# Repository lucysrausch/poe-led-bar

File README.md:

# poe-led-bar

Important! I did not have a chance to write docs for this project yet, so:
The hardware is proven at this point and people have successfully ordered and used PCBs based off this repo, with one exception.

The PCB design has a minor bug with the polarity of one of the LEDs inside the ethernet jack.
In rev1.0 of the PCB design, this is not only causing the LED to not work but also the entire ethernet link, because the LEDs are also used as strapping pins to configure the PHY.

The workaround I used is to use this RJ45 jack, which has a bicolor LED so polarity doesn't matter:
https://www.digikey.com/en/products/detail/adam-tech/MTJ-88TX1-FSD-LV/9832786
You could use https://www.digikey.com/en/products/detail/adam-tech/MTJ-88TX1-LV/9832558 which is in stock.

If you dont particularly care about the LEDs in the jack, you can also just get a passive jack without LEDs and solder a 1k SMD resistor across the pads for the LEDs. That should also work fine to configure the PHY.

I will fix this in a future release so more common jacks like the ones stocked at JLC and LCSC can be used.

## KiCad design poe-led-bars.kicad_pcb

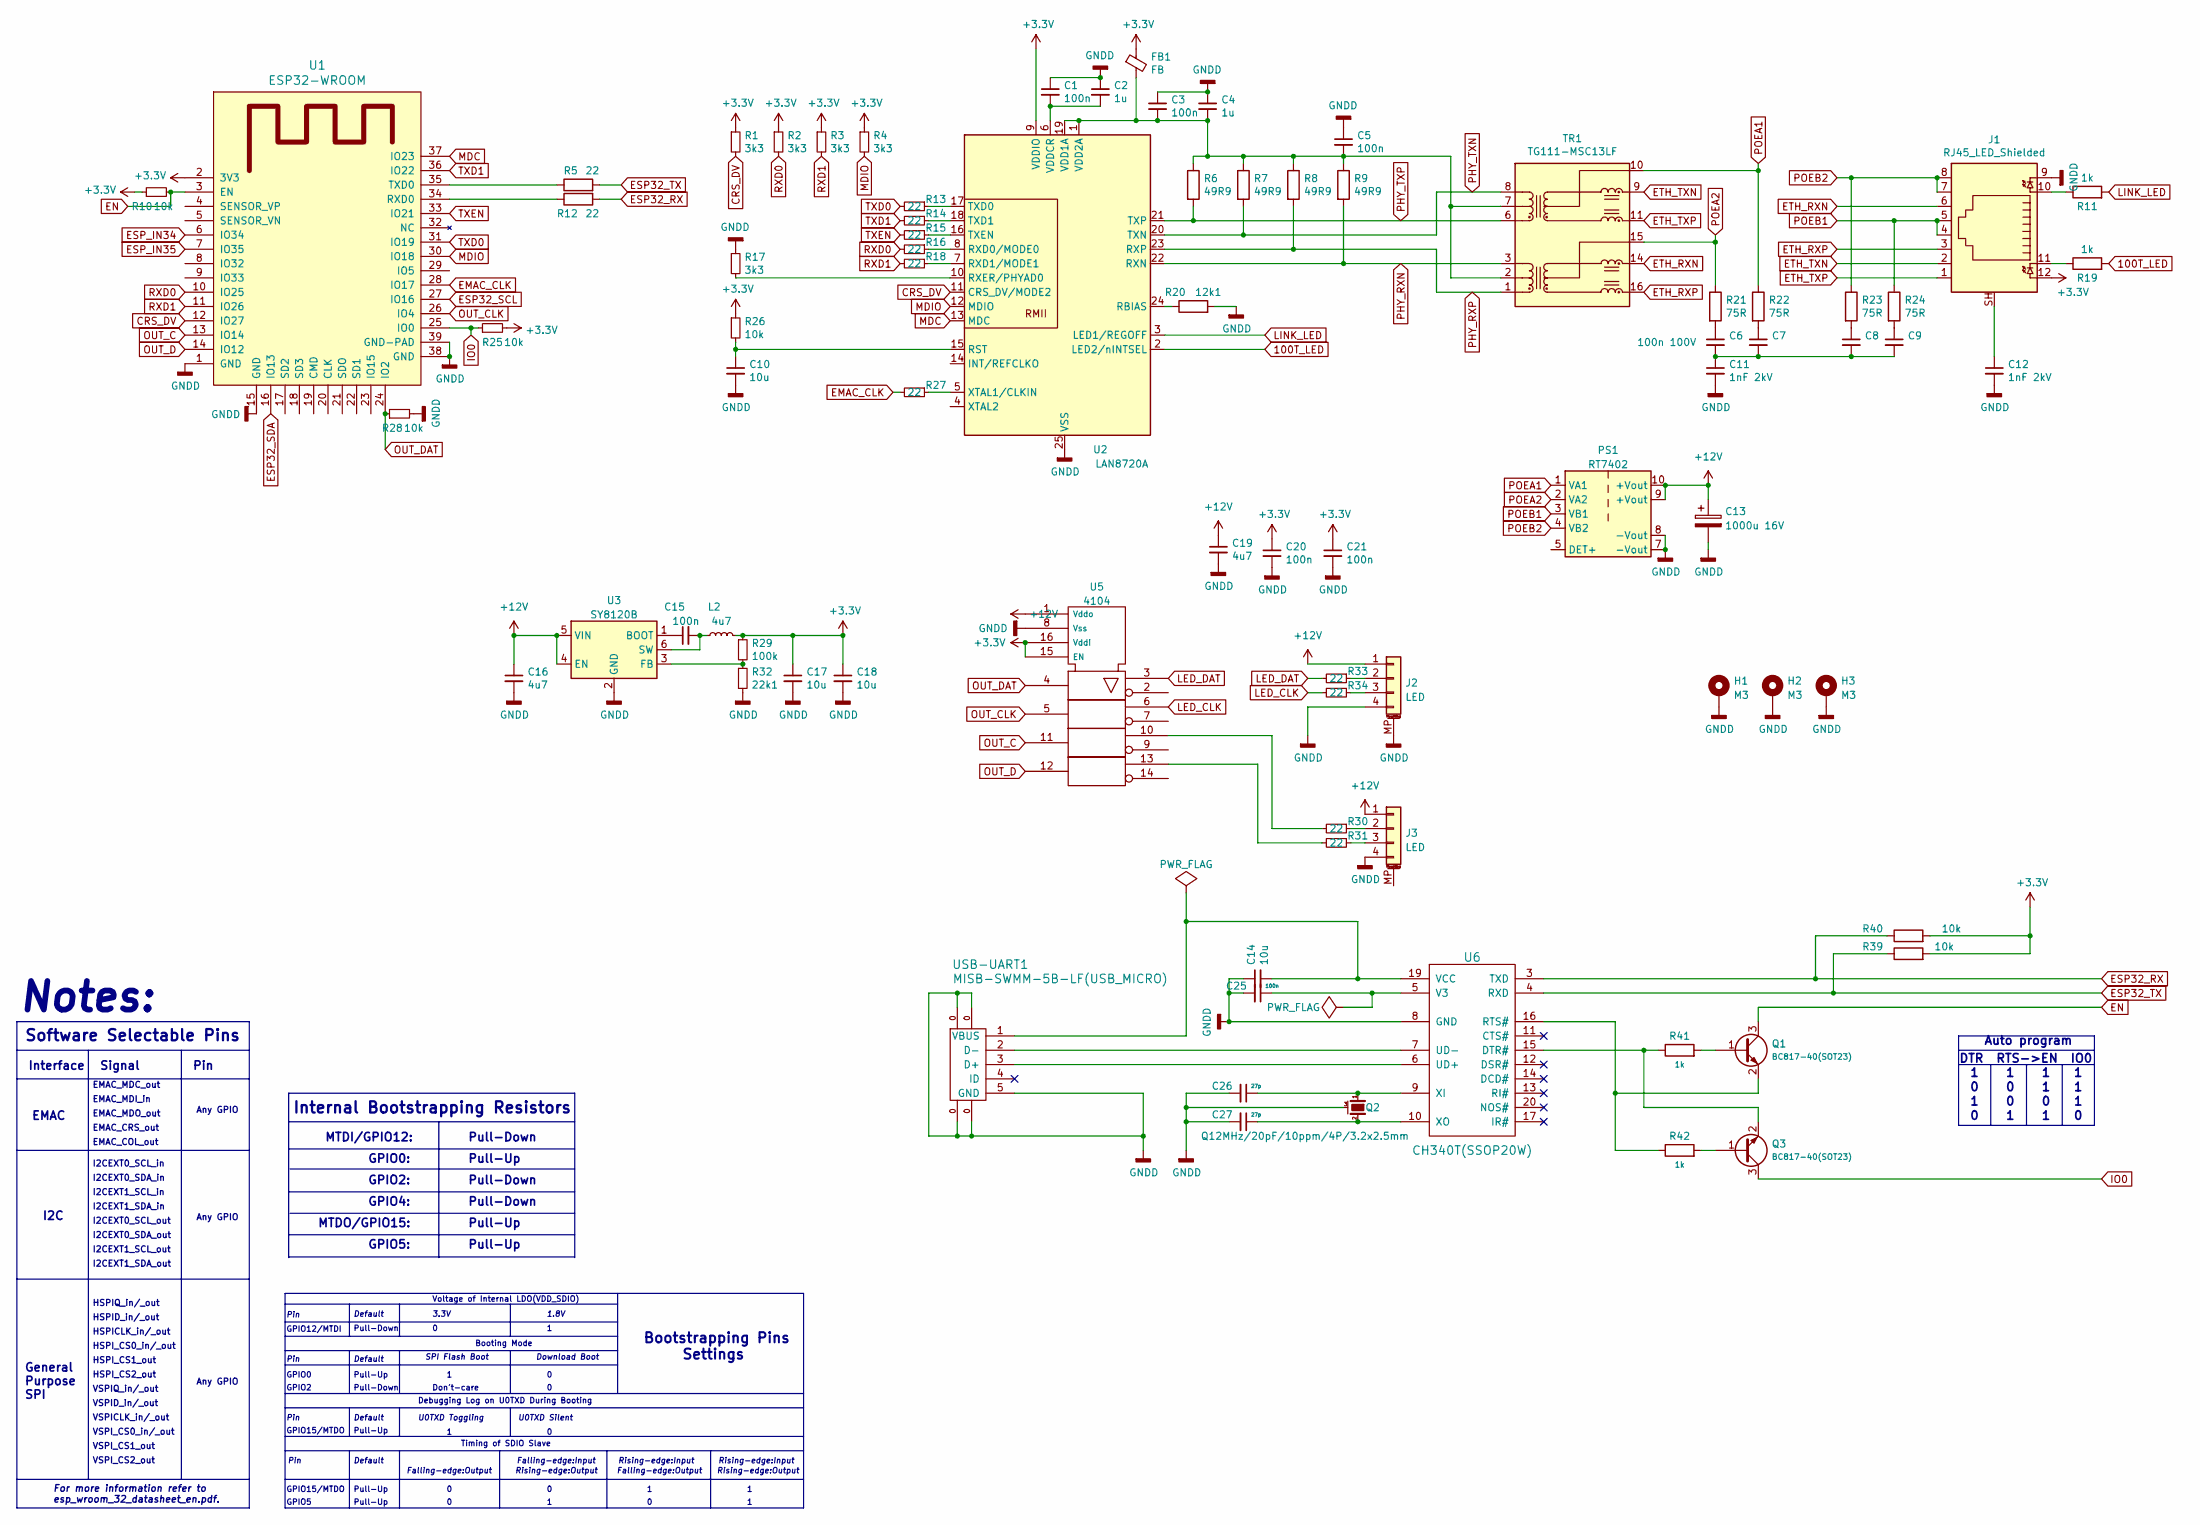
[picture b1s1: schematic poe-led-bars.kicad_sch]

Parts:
C1, C3, C5, C15, C20, C21, C25: 100n; C_0402
C2, C4: 1u; C_0402
C6, C7, C8, C9: 100n 100V; C_0603
C10, C14, C17, C18: 10u; C_0603
C11, C12: 1nF 2kV; C_1206_3216Metric
C13: 1000u 16V
C16, C19: 4u7; C_0603
C26, C27: 27p; C_0402
FB1: FB; L_0402
H1, H2, H3: M3
J1: RJ45_LED_Shielded; RJ45_Cetus_J1B1211CCD_Horizontal
J2, J3: LED
L2: 4u7
PS1: RT7402; Converter_DCDC_XP_POWER-IAxxxxD_THT
Q1, Q3: BC817-40(SOT23); SOT-23
Q2: Q12MHz/20pF/10ppm/4P/3.2x2.5mm; TSX-3.2x2.5mm_GND(3)
R1, R2, R3, R4, R17: 3k3; R_0402
R5, R12, R13, R14, R15, R16, R18, R27, R30, R31, R33, R34: 22; R_0402
R6, R7, R8, R9: 49R9; R_0402
R10, R25, R26, R28, R39, R40: 10k; R_0402
R11, R19, R41, R42: 1k; R_0402
R20: 12k1; R_0402
R21, R22, R23, R24: 75R; R_0402
R29: 100k; R_0402
R32: 22k1; R_0402
TR1: TG111-MSC13LF; XFMR_H1102NLT
U1: ESP32-WROOM; ESP32-WROOM-32U
U2: LAN8720A; QFN-24-1EP_4x4mm_P0.5mm_EP2.6x2.6mm
U3: SY8120B; SOT-23-6
U5: 4104; SO-16_3.9x9.9mm_P1.27mm
U6: CH340T(SSOP20W); SSOP-20W
USB-UART1: MISB-SWMM-5B-LF(USB_MICRO); USB-MICRO_MISB-SWMM-5B_LF

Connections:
100T_LED: R19.2, U2.2 (LED2/nINTSEL)
+3V3: C17.1, C18.1, C20.1, C21.1, FB1.1, J1.12, L2.2, R1.1, R2.1, R3.1, R4.1, R10.1, R25.2, R26.1, R29.1, R39.2, R40.2, U1.2 (3V3), U2.9 (VDDIO), U5.15 (EN), U5.16 (Vddi)
+12V: C13.1, C16.1, C19.1, J2.1, J3.1, PS1.9 (+Vout), PS1.10 (+Vout), U3.4 (EN), U3.5 (VIN), U5.1 (Vddo)
CRS_DV: R1.2, U1.12 (IO27), U2.11 (CRS_DV/MODE2)
EMAC_CLK: R27.2, U1.28 (IO17)
EN: Q1.3 (C), R10.2, U1.3 (EN)
ESP32_RX: R12.2, R40.1, U6.3 (TXD)
ESP32_SCL: U1.27 (IO16)
ESP32_SDA: U1.16 (IO13)
ESP32_TX: R5.2, R39.1, U6.4 (RXD)
ESP_IN34: U1.6 (IO34)
ESP_IN35: U1.7 (IO35)
ETH_RXN: J1.6, TR1.14 (MTX2-)
ETH_RXP: J1.3, TR1.16 (MTX2+)
ETH_TXN: J1.2, TR1.9 (MTX2-)
ETH_TXP: J1.1, TR1.11 (MTX2+)
GNDD: C1.1, C2.1, C3.1, C4.1, C5.1, C10.2, C11.2, C12.2, C13.2, C14.1, C16.2, C17.2, C18.2, C19.2, C20.2, C21.2, C25.2, C26.2, C27.2, H1.1, H2.1, H3.1, J1.9, J2.4, J2.MP (MountPin), J3.4, PS1.7 (-Vout), PS1.8 (-Vout), Q2.3 (case), R17.1, R20.2, R28.2, R32.2, U1.1 (GND), U1.15 (GND), U1.38 (GND), U1.39 (GND-PAD), U2.25 (VSS), U3.2 (GND), U5.8 (Vss), U6.8 (GND), USB-UART1.0, USB-UART1.5 (GND)
IO0: Q3.3 (C), R25.1, U1.25 (IO0)
LED_CLK: R34.2, U5.6
LED_DAT: R33.2, U5.3
LINK_LED: R11.2, U2.3 (LED1/REGOFF)
MDC: U1.37 (IO23), U2.13 (MDC)
MDIO: R4.2, U1.30 (IO18), U2.12 (MDIO)
unnamed: C1.2, C2.2, U2.6 (VDDCR)
unnamed: C3.2, C4.2, C5.2, FB1.2, R6.1, R7.1, R8.1, R9.1, TR1.2 (TCT2), TR1.7 (TCT2), U2.1 (VDD2A), U2.19 (VDD1A)
unnamed: C6.1, R21.2
unnamed: C7.1, R22.2
unnamed: C8.1, R23.2
unnamed: C9.1, R24.2
unnamed: C10.1, R26.2, U2.15 (RST)
unnamed: C6.2, C7.2, C8.2, C9.2, C11.1
unnamed: C12.1, J1.SH
unnamed: C14.2, U6.19 (VCC), USB-UART1.1 (VBUS)
unnamed: C15.1, U3.1 (BOOT)
unnamed: C15.2, L2.1, U3.6 (SW)
unnamed: C25.1, U6.5 (V3)
unnamed: C26.1, Q2.1, U6.9 (XI)
unnamed: C27.1, Q2.2, U6.10 (XO)
unnamed: J1.10, R11.1
unnamed: J1.11, R19.1
unnamed: J2.2, R33.1
unnamed: J2.3, R34.1
unnamed: J3.2, R30.1
unnamed: J3.3, R31.1
unnamed: Q1.1 (B), R41.2
unnamed: Q1.2 (E), R42.1, U6.16 (RTS#)
unnamed: Q3.1 (B), R42.2
unnamed: Q3.2 (E), R41.1, U6.15 (DTR#)
unnamed: R5.1, U1.35 (TXD0)
unnamed: R12.1, U1.34 (RXD0)
unnamed: R13.1, U2.17 (TXD0)
unnamed: R14.1, U2.18 (TXD1)
unnamed: R15.1, U2.16 (TXEN)
unnamed: R16.1, U2.8 (RXD0/MODE0)
unnamed: R17.2, U2.10 (RXER/PHYAD0)
unnamed: R18.1, U2.7 (RXD1/MODE1)
unnamed: R20.1, U2.24 (RBIAS)
unnamed: R27.1, U2.5 (XTAL1/CLKIN)
unnamed: R29.2, R32.1, U3.3 (FB)
unnamed: R30.2, U5.10
unnamed: R31.2, U5.13
unnamed: U6.6 (UD+), USB-UART1.3 (D+)
unnamed: U6.7 (UD-), USB-UART1.2 (D-)
OUT_C: U1.13 (IO14), U5.11
OUT_CLK: U1.26 (IO4), U5.5
OUT_D: U1.14 (IO12), U5.12
OUT_DAT: R28.1, U1.24 (IO2), U5.4
PHY_RXN: R9.2, TR1.3 (TD2-), U2.22 (RXN)
PHY_RXP: R8.2, TR1.1 (TD2+), U2.23 (RXP)
PHY_TXN: R7.2, TR1.8 (TD2-), U2.20 (TXN)
PHY_TXP: R6.2, TR1.6 (TD2+), U2.21 (TXP)
POEA1: PS1.1 (VA1), R22.1, TR1.10 (MCT2)
POEA2: PS1.2 (VA2), R21.1, TR1.15 (MCT2)
POEB1: J1.4, J1.5, PS1.3 (VB1), R24.1
POEB2: J1.7, J1.8, PS1.4 (VB2), R23.1
RXD0: R2.2, R16.2, U1.10 (IO25)
RXD1: R3.2, R18.2, U1.11 (IO26)
TXD0: R13.2, U1.31 (IO19)
TXD1: R14.2, U1.36 (IO22)
TXEN: R15.2, U1.33 (IO21)

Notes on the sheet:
Internal Bootstrapping Resistors
Pull-Up
I2CEXT0_SDA_out
Signal
Booting Mode
Rising-edge:Output
Download Boot
Any GPIO
1.8V
HSPI_CS1_out
Default
GPIO5:
Auto program
Pin
3.3V
GPIO5
Don't-care
GPIO15/MTDO
VSPIQ_in/_out
EMAC_CRS_out
HSPI_CS0_in/_out
GPIO0:
Debugging Log on U0TXD During Booting
I2CEXT0_SDA_in
I2CEXT0_SCL_out
I2C
General Purpose SPI
HSPI_CS2_out
Pull-Down
Software Selectable Pins
I2CEXT0_SCL_in
VSPI_CS0_in/_out
Falling-edge:Input
Voltage of Internal LDO(VDD_SDIO)
Notes:
GPIO2
Rising-edge:Input
VSPI_CS1_out
MTDO/GPIO15:
EMAC_MDI_in

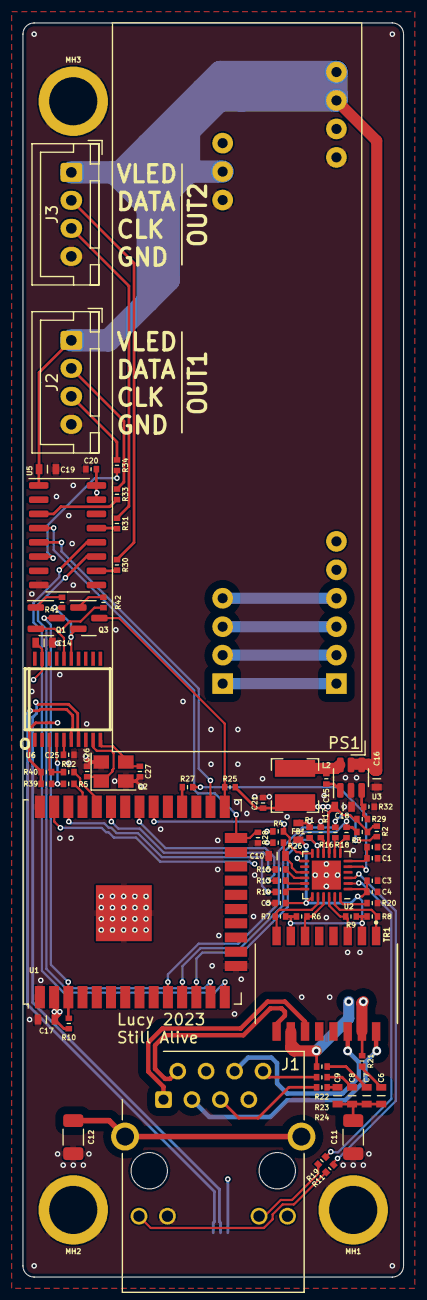
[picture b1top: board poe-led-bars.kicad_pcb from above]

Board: 4 copper layers, 34.0 x 112.0 mm, 80 parts (1 on the bottom side), 76 nets.

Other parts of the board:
MH1, MH2, MH3: Fiducial_0.5mm_Mask1.5mm

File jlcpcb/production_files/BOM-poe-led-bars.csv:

Comment,Designator,Footprint,LCSC
FB,FB1,C_0603,C1002
1k,"R11,R19,R41,R42",R_0402,C11702
100n,"C1,C15,C20,C21,C25,C3,C5",C_0402,C1525
27p,"C26,C27",C_0402,C1557
100n 100V,"C6,C7,C8,C9",C_0603,C15725
4u7,L2,L_Bourns-SRN4018,C167828
22k1,R32,R_0402,C170263
4u7,"C16,C19",C_0603,C19666
22,"R12,R13,R14,R15,R16,R18,R27,R30,R31,R33,R34,R5",R_0402,C25092
49R9,"R6,R7,R8,R9",R_0402,C25120
75R,"R21,R22,R23,R24",R_0402,C25133
100k,R29,R_0402,C25741
10k,"R10,R25,R26,R28,R39,R40",R_0402,C25744
12k1,R20,R_0402,C25852
3k3,"R1,R17,R2,R3,R4",R_0402,C25890
Fiducial_0.5mm_Mask1.5mm,"MH1,MH2,MH3",Fiducial_0.5mm_Mask1.5mm,C2915633
RJ45_LED_Shielded,J1,RJ45_Cetus_J1B1211CCD_Horizontal,C363238
BC817-40(SOT23),"Q1,Q3",SOT-23,C380921
LAN8720A,U2,QFN-24-1EP_4x4mm_P0.5mm_EP2.6x2.6mm,C45223
TG111-MSC13LF,TR1,XFMR_H1102NLT,C510548
1u,"C2,C4",C_0402,C52923
ESP32-WROOM,U1,ESP32-WROOM-32U,C701345
4104,U5,SO-16_3.9x9.9mm_P1.27mm,C7531
CH340T(SSOP20W),U6,SSOP-20W,C8689
SY8120B,U3,SOT-23-6,C88474
1nF 2kV,"C11,C12",C_1206_3216Metric,C9196
10u,"C10,C14,C17,C18",C_0603,C96446
Q12MHz/20pF/10ppm/4P/3.2x2.5mm,Q2,Crystal_SMD_3225-4Pin_3.2x2.5mm,C97231
LED,J3,JST_XH_B4B-XH-A_1x04_P2.50mm_Vertical,
LED,J2,JST_XH_B4B-XH-A_1x04_P2.50mm_Vertical,
RT7402,PS1,Converter_DCDC_XP_POWER-IAxxxxD_THT,

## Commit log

2025-03-14 ADD: pictures and assembly / demo videos :p
2025-03-14 cleanup
2025-10-06 Update README.md to warn ab RJ45 jack
2025-10-06 Update BOM-poe-led-bars.csv to remove wrong RJ45 part
